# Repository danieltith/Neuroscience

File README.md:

# Neuroscience

Code and hardware files related to my PhD thesis: "Mapping associations between early life adversity and alcohol use disorder through human epidemiology and rat neurobiology".

[Link to be inserted once publicly available]

References:

Brown LA, Hasan S, Foster RG and Peirson SN. COMPASS: Continuous Open Mouse Phenotyping of Activity and Sleep Status [version 2; peer review: 4 approved]. Wellcome Open Res (2017) 1:2. (https://doi.org/10.12688/wellcomeopenres.9892.2)

Akam T, Lustig A, Rowland JM, Kapanaiah SKT, Esteve-Agraz J, Panniello M, Márquez C, Kohl MM, Kätzel D, Costa RM, Walton ME. Open-source, Python-based, hardware and software for controlling behavioural neuroscience experiments. eLife (2022) 11:e67846. (https://doi.org/10.7554/eLife.67846)

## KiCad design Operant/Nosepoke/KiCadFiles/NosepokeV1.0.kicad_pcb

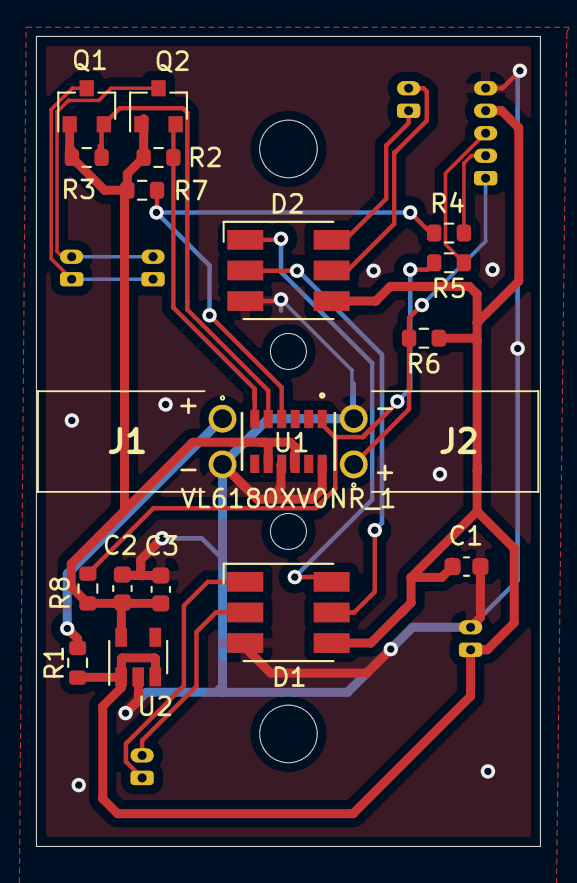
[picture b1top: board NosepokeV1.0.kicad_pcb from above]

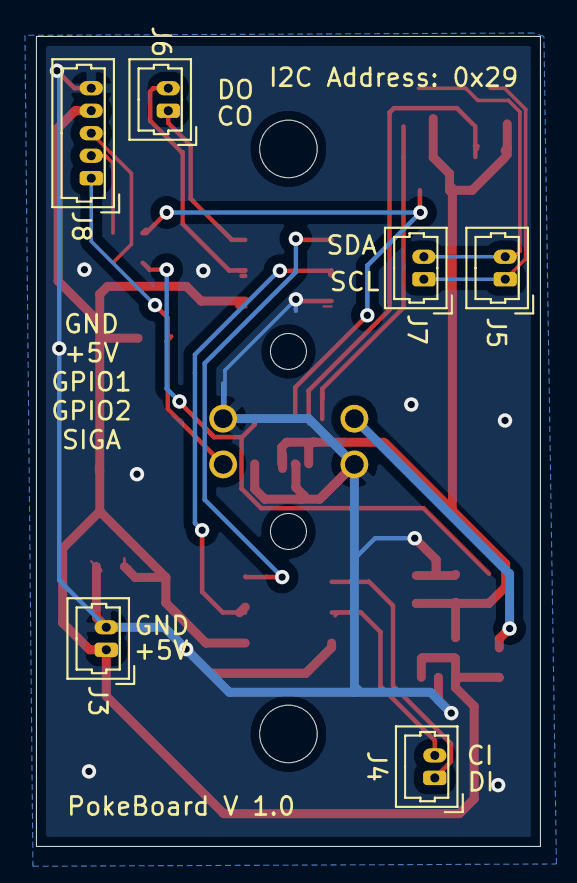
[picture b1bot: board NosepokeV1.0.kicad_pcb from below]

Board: 2 copper layers, 28.0 x 45.0 mm, 27 parts (6 on the bottom side), 19 nets.

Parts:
C1, C2: 10uF; C_0603_1608Metric
C3: 100nF; C_0603_1608Metric
D1: DotstarRGB; LED_RGB_5050-6
D2: DotstarWhite; LED_RGB_5050-6
J1, J2: SSW-102-02-T-S-RA; SSW-102-XX-YYY-S-RA
J3: 5V power in; Molex_PicoBlade_53047-0210_1x02_P1.25mm_Vertical
J4: SPI in; Molex_PicoBlade_53047-0210_1x02_P1.25mm_Vertical
J5: I2C in; Molex_PicoBlade_53047-0210_1x02_P1.25mm_Vertical
J6: SPI out; Molex_PicoBlade_53047-0210_1x02_P1.25mm_Vertical
J7: I2C out; Molex_PicoBlade_53047-0210_1x02_P1.25mm_Vertical
J8: Conn_01x03; Molex_PicoBlade_53047-0510_1x05_P1.25mm_Vertical
Mount1, Mount2: MountingHole_3.2mm_M3
Q1, Q2: BSS138; SOT-23
R1: 220R; R_0603_1608Metric
R2, R3, R4, R5, R6: 10K; R_0603_1608Metric
R7, R8: 47K; R_0603_1608Metric
U1: VL6180XV0NR_1; VL6180XV0NR&slash_1
U2: LP5907MFX-2.8; SOT-23-5

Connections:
+2V8: C2.1, C3.1, Q1.1, Q2.1, R2.1, R3.1, R7.1, R8.1, U1.8, U1.10, U2.5
+5V: C1.1, D1.4, D2.4, J3.1, J8.4, R1.1, R6.1, U2.1, U2.3
CI: D1.2, J4.2
CO: D2.5, J6.2
DI: D1.1, J4.1
DO: D2.6, J6.1
GND: C1.2, C2.2, C3.2, D1.3, D2.3, J1.2, J2.2, J3.2, J8.5, U1.9, U1.12, U2.2
GPIO0: J8.2, R4.1
GPIO1: J8.3, R5.1
unnamed: D1.5, D2.2
unnamed: D1.6, D2.1
unnamed: J1.1, R1.2
unnamed: R4.2, R7.2, U1.4
unnamed: R5.2, R8.2, U1.1
SCL: J5.1, J7.1, Q1.3
SCL_LV: Q1.2, R3.2, U1.5
SDA: J5.2, J7.2, Q2.3
SDA_LV: Q2.2, R2.2, U1.6
Sig_A: J2.1, J8.1, R6.2

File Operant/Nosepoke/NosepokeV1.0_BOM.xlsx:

Part Number | Designator | Description | Mount | Quantity | Manufacturer | Manufacturer PN | Supplier | Supplier PN
1 | C1,C2 | 10 uF Capacitor 0603 | SMD | 2 |  |  | Newbury free stock | 0603-10uF-6.3V
2 | C3 | 100nF Capacitor 0603 | SMD | 1 |  |  | Newbury free stock | 0603-100nF-25V
3 | J1,J2 | Right angle header | THT | 2 | SAMTEC | SSW-102-02-T-S-RA | Digikey | SAM11929-ND
4 | J3,J4,J5,J6,J7 | 2 pin connector | THT | 5 | Molex | 530470210 | Digikey | 455-1611-ND
5 | J8 | 5 pin connector | THT | 1 | Molex | 530470510 | Digikey | WM1734-ND
6 | Q1,Q2 | Mosfet | SMD | 2 |  | BSS138 | Farnell | 9845330
7 | R1 | 220R resistor 0603 | SMD | 1 |  |  | Newbury free stock | 0603-220R
8 | R2,R3,R4,R5,R6 | 10k resistor 0603 | SMD | 5 |  |  | Newbury free stock | 0603-10k
9 | R7,R8 | 47k resistor 0603 | SMD | 2 |  |  | Newbury free stock | 0603-47K
10 | U1 | TOF sensor | Leadless | 1 | ST Microelectronics | VL6180XV0NR/1 | Digikey | 497-14702-1-ND
11 | U2 | LP5907 2.8V LDO | SMD | 1 | TEXAS INSTRUMENTS | LP5907MFX-2.8/NOPB | Farnell | 3007717

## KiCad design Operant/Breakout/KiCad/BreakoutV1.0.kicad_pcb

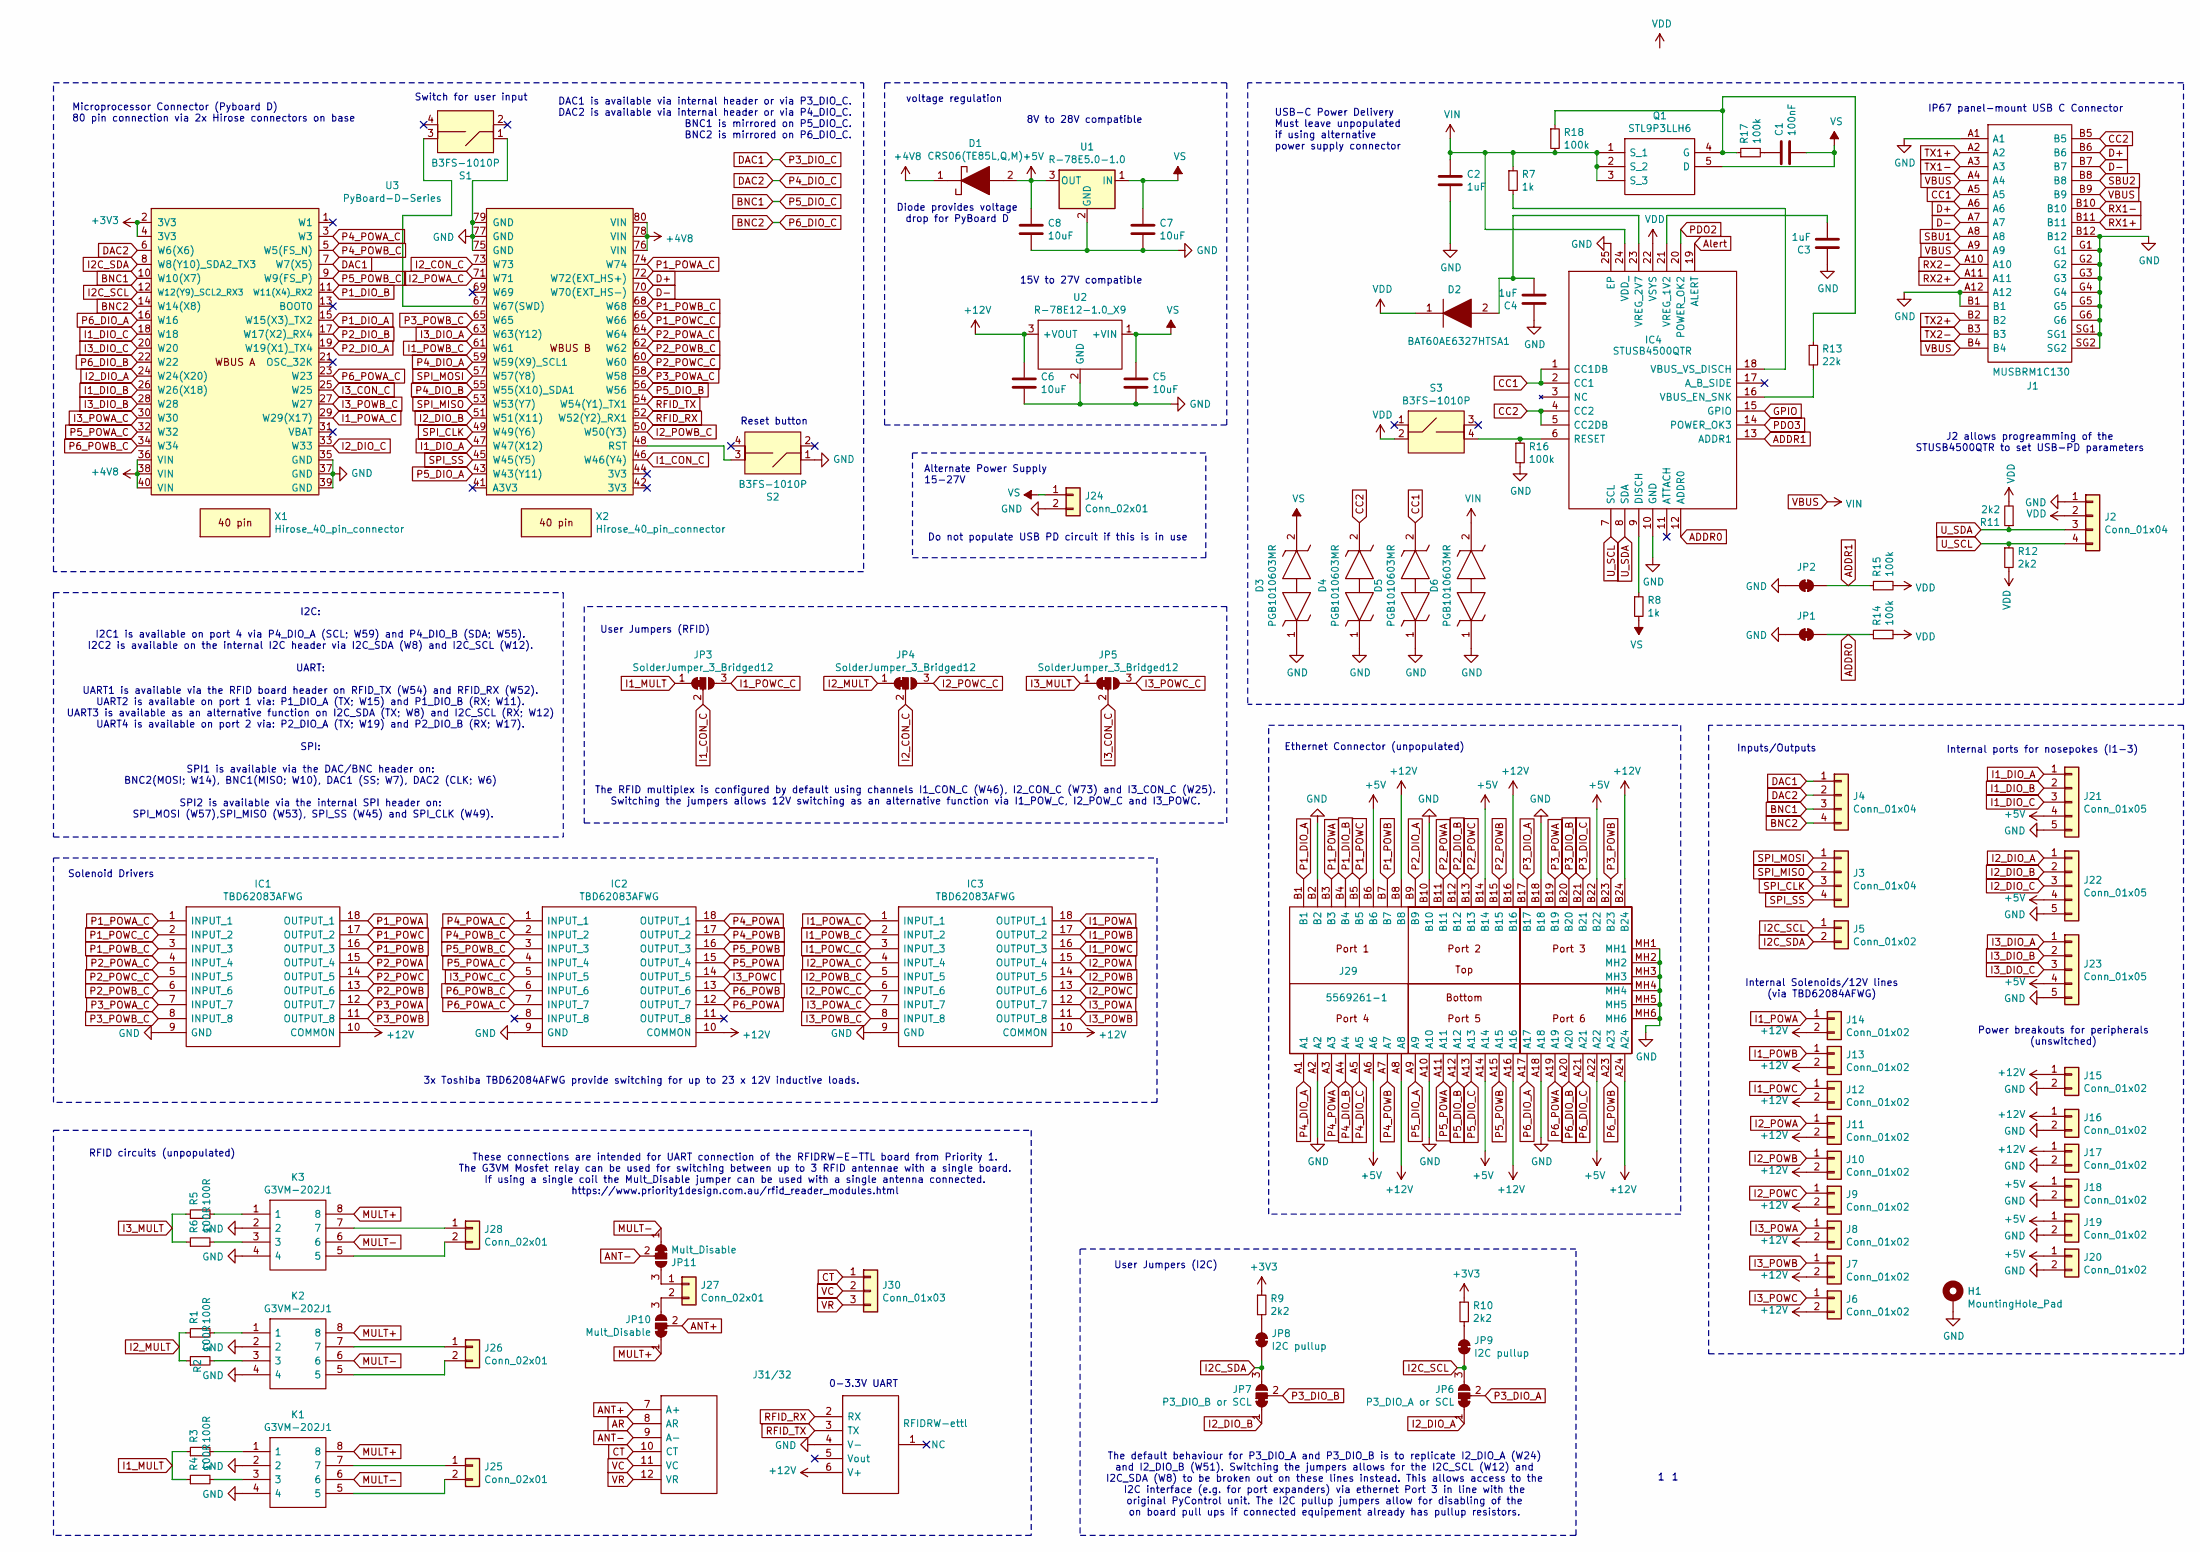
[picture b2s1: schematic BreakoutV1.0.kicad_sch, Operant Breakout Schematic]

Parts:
C1: 100nF; C_0805_2012Metric
C2, C3, C4: 1uF; C_0603_1608Metric
C5, C6, C7, C8: 10uF; C_1206_3216Metric
D1: CRS06(TE85L,Q,M); S-FLAT-2; Mouser Part Number 863-MBR120VLSFT3G
D2: BAT60AE6327HTSA1; SOD2513X110N; Mouser Part Number 726-BAT60AE6327HTSA1
D3, D4, D5, D6: PGB1010603MR; Mouser Part Number 576-PGB1010603MR
H1: MountingHole_Pad; SolderWirePad_single_1-2mmDrill
IC1, IC2, IC3: TBD62083AFWG; SOIC127P1030X245-18N; Mouser Part Number 757-TBD62083APG
IC4: STUSB4500QTR; QFN50P400X400X100-25N-D; Mouser Part Number 511-STUSB4500QTR
J1: MUSBRM1C130; Mouser Part Number 523-MUSBRM1C130
J2, J3, J4: Conn_01x04; Molex_PicoBlade_53047-0410_1x04_P1.25mm_Vertical
J5, J6, J7, J8, J9, J10, J11, J12, J13, J14, J15, J16, J17, J18, J19, J20: Conn_01x02; Molex_PicoBlade_53047-0210_1x02_P1.25mm_Vertical
J21, J22, J23: Conn_01x05; Molex_PicoBlade_53047-0510_1x05_P1.25mm_Vertical
J24, J25, J26, J27, J28: Conn_02x01; JST_EH_B2B-EH-A_1x02_P2.50mm_Vertical
J29: 5569261-1; 55692611; Mouser Part Number 571-5569261-1
J30: Conn_01x03; SolderWirePad_3x_0-8mmDrill2
J31/32: RFIDRW-ettl; Manufacturer_Part_Number RFIDRW-e-ttl
JP1, JP2: SolderJumper_2_Bridged; SolderJumper-2_P1.3mm_Bridged_RoundedPad1.0x1.5mm
JP3, JP4, JP5: SolderJumper_3_Bridged12; SolderJumper-3_P1.3mm_Bridged12_RoundedPad1.0x1.5mm_NumberL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
JP6: P3_DIO_A or SCL; SolderJumper-3_P1.3mm_Bridged12_RoundedPad1.0x1.5mm_NumberL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
JP7: P3_DIO_B or SCL; SolderJumper-3_P1.3mm_Bridged12_RoundedPad1.0x1.5mm_NumberL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
JP8, JP9: I2C pullup; SolderJumper-2_P1.3mm_Bridged_RoundedPad1.0x1.5mm
JP10, JP11: Mult_Disable; SolderJumper-3_P1.3mm_Bridged12_RoundedPad1.0x1.5mm_NumberL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
K1, K2, K3: G3VM-202J1; SOP254P700X210-8N; Mouser Part Number 653-G3VM-202J1
Q1: STL9P3LLH6; STL20N6F7; Mouser Part Number 511-STL9P3LLH6
R1, R2, R3, R4, R5, R6: 100R; R_0603_1608Metric
R7, R8: 1k; R_0603_1608Metric
R9, R10, R11, R12: 2k2; R_0603_1608Metric
R13: 22k; R_0603_1608Metric
R14, R15, R16, R17, R18: 100k; R_0603_1608Metric
S1, S2, S3: B3FS-1010P; 6mm_tactile_smd
U1: R-78E5.0-1.0; Converter_DCDC_RECOM_R-78E-0.5_THT
U2: R-78E12-1.0_X9; Converter_DCDC_RECOM_R-78E-0.5_THT; Mouser Part Number 919-R-78E12-1.0/X9
U3: PyBoard-D-Series; PyBoard_D-Series
X1, X2: Hirose_40_pin_connector; Hirose_40_pin

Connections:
+3V3: R9.1, R10.1, U3.2 (3V3), U3.4 (3V3)
+4V8: D1.1, U3.36 (VIN), U3.38 (VIN), U3.40 (VIN), U3.76 (VIN), U3.78 (VIN), U3.80 (VIN)
+5V: C8.1, D1.2, J18.1, J19.1, J20.1, J21.4, J22.4, J23.4, J29.A6, J29.A14, J29.A22, J29.B6, J29.B14, J29.B22, U1.3 (OUT)
+12V: C6.1, IC1.10 (COMMON), IC2.10 (COMMON), IC3.10 (COMMON), J6.2, J7.2, J8.2, J9.2, J10.2, J11.2, J12.2, J13.2, J14.2, J15.1, J16.1, J17.1, J29.A8, J29.A16, J29.A24, J29.B8, J29.B16, J29.B24, J31/32.6 (V+), U2.3 (+VOUT)
ADDR0: IC4.12 (ADDR0), JP1.1 (A), R14.1
ADDR1: IC4.13 (ADDR1), JP2.1 (A), R15.1
ANT+: J31/32.7 (A+), JP10.2 (C)
ANT-: J31/32.9 (A-), JP11.2 (C)
AR: J31/32.8 (AR)
Alert: IC4.19 (ALERT)
BNC1: J4.3, J29.A13, U3.10 (W10(X7))
BNC2: J4.4, J29.A21, U3.14 (W14(X8))
CC1: D5.2, IC4.1 (CC1DB), IC4.2 (CC1), J1.A5
CC2: D4.2, IC4.4 (CC2), IC4.5 (CC2DB), J1.B5
CT: J30.1, J31/32.10 (CT)
D+: J1.A6, J1.B6, U3.72 (W72(EXT_HS+))
D-: J1.A7, J1.B7, U3.70 (W70(EXT_HS-))
DAC1: J4.1, J29.B21, U3.7 (W7(X5))
DAC2: J4.2, J29.A5, U3.6 (W6(X6))
GND: C2.2, C3.1, C4.1, C5.2, C6.2, C7.2, C8.2, D3.1, D4.1, D5.1, D6.1, H1.1, IC1.9 (GND), IC2.9 (GND), IC3.9 (GND), IC4.10 (GND), IC4.25 (EP), J1.A1, J1.A12, J1.B1, J1.B12, J1.G1, J1.G2, J1.G3, J1.G4, J1.G5, J1.G6, J1.SG1, J1.SG2, J2.1, J15.2, J16.2, J17.2, J18.2, J19.2, J20.2, J21.5, J22.5, J23.5, J24.2, J29.A2, J29.A10, J29.A18, J29.B2, J29.B10, J29.B18, J29.MH1, J29.MH2, J29.MH3, J29.MH4, J29.MH5, J29.MH6, J31/32.4 (V-), JP1.2 (B), JP2.2 (B), K1.2, K1.4, K2.2, K2.4, K3.2, K3.4, R16.2, S1.1 (in1), S2.1 (in1), U1.2 (GND), U2.2 (GND), U3.35 (GND), U3.37 (GND), U3.39 (GND), U3.75 (GND), U3.77 (GND), U3.79 (GND)
GPIO: IC4.15 (GPIO)
I1_CON_C: JP3.2 (C), U3.46 (W46(Y4))
I1_DIO_A: J21.1, U3.47 (W47(X12))
I1_DIO_B: J21.2, U3.26 (W26(X18))
I1_DIO_C: J21.3, U3.18 (W18)
I1_MULT: JP3.1 (A), R3.1, R4.1
I1_POWA: IC3.18 (OUTPUT_1), J14.1
I1_POWA_C: IC3.1 (INPUT_1), U3.29 (W29(X17))
I1_POWB: IC3.17 (OUTPUT_2), J13.1
I1_POWB_C: IC3.2 (INPUT_2), U3.61 (W61)
I1_POWC: IC3.16 (OUTPUT_3), J12.1
I1_POWC_C: IC3.3 (INPUT_3), JP3.3 (B)
I2C_SCL: J5.1, JP6.3 (B), JP9.2 (B), U3.12 (W12(Y9)_SCL2_RX3)
I2C_SDA: J5.2, JP7.3 (B), JP8.2 (B), U3.8 (W8(Y10)_SDA2_TX3)
I2_CON_C: JP4.2 (C), U3.73 (W73)
I2_DIO_A: J22.1, JP6.1 (A), U3.24 (W24(X20))
I2_DIO_B: J22.2, JP7.1 (A), U3.51 (W51(X11))
I2_DIO_C: J22.3, U3.33 (W33)
I2_MULT: JP4.1 (A), R1.1, R2.1
I2_POWA: IC3.15 (OUTPUT_4), J11.1
I2_POWA_C: IC3.4 (INPUT_4), U3.71 (W71)
I2_POWB: IC3.14 (OUTPUT_5), J10.1
I2_POWB_C: IC3.5 (INPUT_5), U3.50 (W50(Y3))
I2_POWC: IC3.13 (OUTPUT_6), J9.1
I2_POWC_C: IC3.6 (INPUT_6), JP4.3 (B)
I3_CON_C: JP5.2 (C), U3.25 (W25)
I3_DIO_A: J23.1, U3.63 (W63(Y12))
I3_DIO_B: J23.2, U3.28 (W28)
I3_DIO_C: J23.3, U3.20 (W20)
I3_MULT: JP5.1 (A), R5.1, R6.1
I3_POWA: IC3.12 (OUTPUT_7), J8.1
I3_POWA_C: IC3.7 (INPUT_7), U3.30 (W30)
I3_POWB: IC3.11 (OUTPUT_8), J7.1
I3_POWB_C: IC3.8 (INPUT_8), U3.27 (W27)
I3_POWC: IC2.14 (OUTPUT_5), J6.1
I3_POWC_C: IC2.5 (INPUT_5), JP5.3 (B)
MULT+: JP10.1 (A), K1.8, K2.8, K3.8
MULT-: JP11.1 (A), K1.6, K2.6, K3.6
unnamed: C1.1, R17.2
unnamed: C3.2, IC4.21 (VREG_1V2)
unnamed: C4.2, D2.2, IC4.23 (VREG_2V7)
unnamed: IC4.6 (RESET), R16.1, S3.4 (out2)
unnamed: IC4.9 (DISCH), R8.1
unnamed: IC4.16 (VBUS_EN_SNK), R13.2
unnamed: IC4.18 (VBUS_VS_DISCH), R7.2
unnamed: J25.1, K1.7
unnamed: J25.2, K1.5
unnamed: J26.1, K2.7
unnamed: J26.2, K2.5
unnamed: J27.1, JP11.3 (B)
unnamed: J27.2, JP10.3 (B)
unnamed: J28.1, K3.7
unnamed: J28.2, K3.5
unnamed: JP8.1 (A), R9.2
unnamed: JP9.1 (A), R10.2
unnamed: K1.1, R3.2
unnamed: K1.3, R4.2
unnamed: K2.1, R1.2
unnamed: K2.3, R2.2
unnamed: K3.1, R5.2
unnamed: K3.3, R6.2
unnamed: Q1.4 (G), R13.1, R17.1, R18.1
unnamed: S1.3 (out1), U3.67 (W67(SWD))
unnamed: S2.3 (out1), U3.48 (RST)
P1_DIO_A: J29.B1, U3.15 (W15(X3)_TX2)
P1_DIO_B: J29.B4, U3.11 (W11(X4)_RX2)
P1_POWA: IC1.18 (OUTPUT_1), J29.B3
P1_POWA_C: IC1.1 (INPUT_1), U3.74 (W74)
P1_POWB: IC1.16 (OUTPUT_3), J29.B7
P1_POWB_C: IC1.3 (INPUT_3), U3.68 (W68)
P1_POWC: IC1.17 (OUTPUT_2), J29.B5
P1_POWC_C: IC1.2 (INPUT_2), U3.66 (W66)
P2_DIO_A: J29.B9, U3.19 (W19(X1)_TX4)
P2_DIO_B: J29.B12, U3.17 (W17(X2)_RX4)
P2_POWA: IC1.15 (OUTPUT_4), J29.B11
P2_POWA_C: IC1.4 (INPUT_4), U3.64 (W64)
P2_POWB: IC1.13 (OUTPUT_6), J29.B15
P2_POWB_C: IC1.6 (INPUT_6), U3.62 (W62)
P2_POWC: IC1.14 (OUTPUT_5), J29.B13
P2_POWC_C: IC1.5 (INPUT_5), U3.60 (W60)
P3_DIO_A: J29.B17, JP6.2 (C)
P3_DIO_B: J29.B20, JP7.2 (C)
P3_POWA: IC1.12 (OUTPUT_7), J29.B19
P3_POWA_C: IC1.7 (INPUT_7), U3.58 (W58)
P3_POWB: IC1.11 (OUTPUT_8), J29.B23
P3_POWB_C: IC1.8 (INPUT_8), U3.65 (W65)
P4_DIO_A: J29.A1, U3.59 (W59(X9)_SCL1)
P4_DIO_B: J29.A4, U3.55 (W55(X10)_SDA1)
P4_POWA: IC2.18 (OUTPUT_1), J29.A3
P4_POWA_C: IC2.1 (INPUT_1), U3.3 (W3)
P4_POWB: IC2.17 (OUTPUT_2), J29.A7
P4_POWB_C: IC2.2 (INPUT_2), U3.5 (W5(FS_N))
P5_DIO_A: J29.A9, U3.43 (W43(Y11))
P5_DIO_B: J29.A12, U3.56 (W56)
P5_POWA: IC2.15 (OUTPUT_4), J29.A11
P5_POWA_C: IC2.4 (INPUT_4), U3.32 (W32)
P5_POWB: IC2.16 (OUTPUT_3), J29.A15
P5_POWB_C: IC2.3 (INPUT_3), U3.9 (W9(FS_P))
P6_DIO_A: J29.A17, U3.16 (W16)
P6_DIO_B: J29.A20, U3.22 (W22)
P6_POWA: IC2.12 (OUTPUT_7), J29.A19
P6_POWA_C: IC2.7 (INPUT_7), U3.23 (W23)
P6_POWB: IC2.13 (OUTPUT_6), J29.A23
P6_POWB_C: IC2.6 (INPUT_6), U3.34 (W34)
PDO2: IC4.20 (POWER_OK2)
PDO3: IC4.14 (POWER_OK3)
RFID_RX: J31/32.2 (RX), U3.52 (W52(Y2)_RX1)
RFID_TX: J31/32.3 (TX), U3.54 (W54(Y1)_TX1)
RX1+: J1.B11
RX1-: J1.B10
RX2+: J1.A11
RX2-: J1.A10
SBU1: J1.A8
SBU2: J1.B8
SPI_CLK: J3.3, U3.49 (W49(Y6))
SPI_MISO: J3.2, U3.53 (W53(Y7))
SPI_MOSI: J3.1, U3.57 (W57(Y8))
SPI_SS: J3.4, U3.45 (W45(Y5))
TX1+: J1.A2
TX1-: J1.A3
TX2+: J1.B2
TX2-: J1.B3
U_SCL: IC4.7 (SCL), J2.4, R12.1
U_SDA: IC4.8 (SDA), J2.3, R11.1
VBUS: C2.1, D6.2, IC4.24 (VDD_), J1.A4, J1.A9, J1.B4, J1.B9, Q1.1 (S_1), Q1.2 (S_2), Q1.3 (S_3), R7.1, R18.2
VC: J30.2, J31/32.11 (VC)
VDD: D2.1, IC4.22 (VSYS), J2.2, R11.2, R12.2, R14.2, R15.2, S3.2 (in2)
VR: J30.3, J31/32.12 (VR)
VS: C1.2, C5.1, C7.1, D3.2, J24.1, Q1.5 (D), R8.2, U1.1 (IN), U2.1 (+VIN)

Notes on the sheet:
IP67 panel-mount USB C Connector
The RFID multiplex is configured by default using channels I1_CON_C (W46), I2_CON_C (W73) and I3_CON_C (W25). Switching the jumpers allows 12V switching as an alternative function via I1_POW_C, I2_POW_C and I3_POWC.
8V to 28V compatible
Alternate Power Supply 15-27V
J2 allows progreamming of the STUSB4500QTR to set USB-PD parameters
User Jumpers (RFID)
DAC1 is available via internal header or via P3_DIO_C. DAC2 is available via internal header or via P4_DIO_C. BNC1 is mirrored on P5_DIO_C. BNC2 is mirrored on P6_DIO_C.
3x Toshiba TBD62084AFWG provide switching for up to 23 x 12V inductive loads.
15V to 27V compatible
USB-C Power Delivery Must leave unpopulated if using alternative power supply connector
Do not populate USB PD circuit if this is in use
I2C: I2C1 is available on port 4 via P4_DIO_A (SCL; W59) and P4_DIO_B (SDA; W55). I2C2 is available on the internal I2C header via I2C_SDA (W8) and I2C_SCL (W12). UART: UART1 is available via the RFID board header on RFID_TX (W54) and RFID_RX (W52). UART2 is available on port 1 via: P1_DIO_A (TX; W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
User Jumpers (I2C)
Reset button
Switch for user input
Microprocessor Connector (Pyboard D) 80 pin connection via 2x Hirose connectors on base
voltage regulation
Diode provides voltage drop for PyBoard D
Ethernet Connector (unpopulated)
Power breakouts for peripherals (unswitched)
Internal ports for nosepokes (I1-3)
The default behaviour for P3_DIO_A and P3_DIO_B is to replicate I2_DIO_A (W24) and I2_DIO_B (W51). Switching the jumpers allows for the I2C_SCL (W12) and I2C_SDA (W8) to be broken out on these lines instead. This allows access to the I2C interface (e.g. for port expanders) via ethernet Port 3 in li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
Inputs/Outputs
Internal Solenoids/12V lines (via TBD62084AFWG)
RFID circuits (unpopulated)
These connections are intended for UART connection of the RFIDRW-E-TTL board from Priority 1. The G3VM Mosfet relay can be used for switching between up to 3 RFID antennae with a single board. If using a single coil the Mult_Disable jumper can be used with a single antenna connected. https://www.pr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
Solenoid Drivers
0-3.3V UART

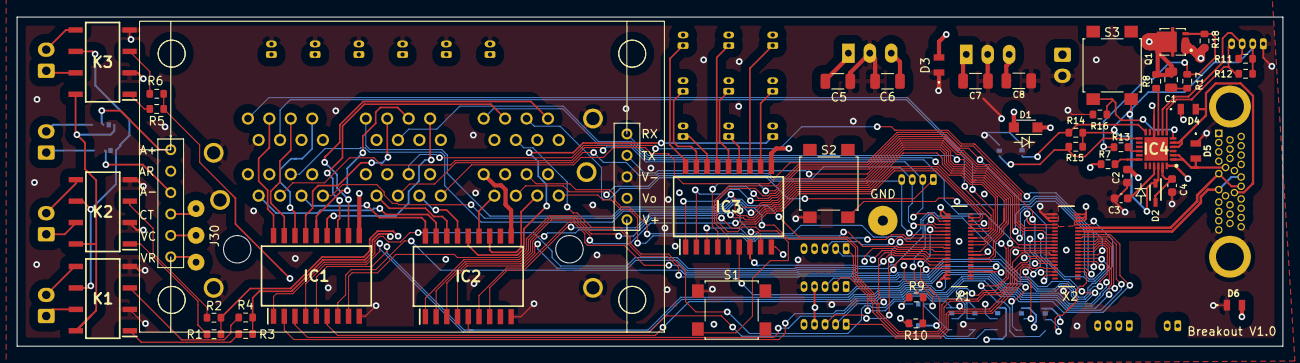
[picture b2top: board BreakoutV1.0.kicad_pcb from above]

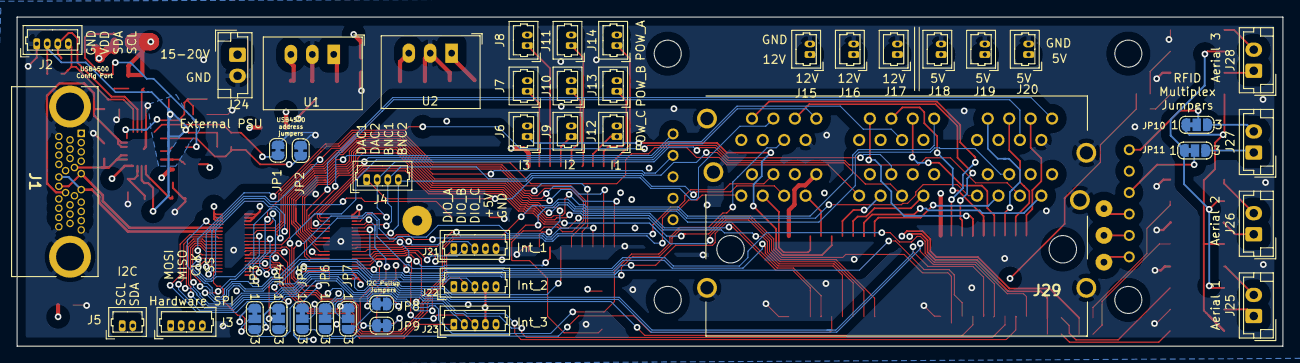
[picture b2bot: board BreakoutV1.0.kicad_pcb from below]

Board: 4 copper layers, 150.0 x 39.0 mm, 91 parts (42 on the bottom side), 134 nets.

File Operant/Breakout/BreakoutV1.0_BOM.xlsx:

Part Number | Designator | Description | Mount | Required Quantitiy | Manufacturer | Manufacturer PN | Supplier | Supplier PN
1 | C1 | Ceramic Capacitor 100V 100nF 0805 | SMD | 1 | KEMET | C0805C104K1RAC7210 | Digikey | 399-C0805C104K1RAC7210CT-ND
2 | C2,C3,C4 | Capacitor 16V 1uF 0603 | SMD | 3 |  |  | Newbury free stock | 0603-1uF-16V
3 | C5,C6,C7,C8 | Capacitor 25V 10uF 1206 | SMD | 4 |  |  | Newbury free stock | 1206-10uf-25V
4 | D1 | Diode Schottky 20V 1A | SMD | 1 | Toshiba | CRS06(TE85L,Q,M) | Digikey | CRS06QMCT-ND
5 | D2 | Diode Schottky 10V 3A | SMD | 1 | Infineon | BAT60AE6327HTSA1 | Digikey | BAT60AE6327HTSA1CT-ND
6 | D3,D4,D5,D6 | Diode TVS 24V 0603 | SMD | 4 | Littelfuse | PGB1010603MR | Digikey | F3801CT-ND
7 | IC1,IC2,IC3 | Driver Array | SMD | 3 | Toshiba | TBD62083AFWG | Digikey | TBD62083AFWGELCT-ND
8 | IC4 | USB TYPE-C PD CTRL, -40 TO 105DEG C | QFN | 1 | STMICROELECTRONICS | STUSB4500QTR | Digikey | 497-18060-1-ND
9 | J1 | USB-C connector | THT | 1 | Amphenol ICC (Commercial Products) | MUSBRM1C130 | Digikey | MUSBRM1C130-ND
10 | J2,J3,J4 | 4 pin through hole connector | THT | 3 | Molex | 530470410 | Digikey | WM1733-ND
11 | J5,J6,J7,J8,J9,J10,J11,J12,J13,J14,J15,J16,J17,J18,J19,J20 | 2 pin through hole connector | THT | 16 | Molex | 530470210 | Digikey | WM1731-ND
12 | J21,J22,J23 | 5 pin through hole connector | THT | 3 | Molex | 530470510 | Digikey | WM1734-ND
13 | Q1 | Power MOSFET | SMD | 1 | STMICROELECTRONICS | STL9P3LLH6 | Digikey | 497-17897-1-ND
14 | R1,R2,R3,R4,R5,R6 | 100 resistor; 0603; 0.1W | SMD | 6 |  |  | Newbury free stock | 0603-100R
15 | R7,R8 | 1k resistor; 0603; 0.1W | SMD | 2 |  |  | Newbury free stock | 0603-1K
16 | R9,R10,R11,R12 | 2.2k resistor; 0603; 0.1W | SMD | 4 |  |  | Newbury free stock | 0603-2K2
17 | R13 | 22k resistor; 0603; 0.1W | SMD | 1 |  |  | Newbury free stock | 0603-22K
18 | R14,R15,R16,R17,R18 | 100k resistor; 0603; 0.1W | SMD | 5 |  |  | Newbury free stock | 0603-100K
19 | S1,S2,S3 | SPST push switch | SMD | 3 | OMRON | B3FS-1012P | Digikey | SW1440CT-ND
20 | U1 | 5V 1A DC DC Converter | THT | 1 | Recom Power | R-78E5.0-1.0 | Digikey | 945-2201-ND
21 | U2 | 12V 1A DC DC Converter | THT | 1 | Recom Power | R-78E12-1.0/X9 | Digikey | 945-R-78E12-1.0/X9-ND
22 | X1,X2 | WBUS40 connector | SMD | 2 | Hirose Electric Co Ltd | DF40HC(4.0)-40DS-0.4V(70) | Digikey | H124604CT-ND

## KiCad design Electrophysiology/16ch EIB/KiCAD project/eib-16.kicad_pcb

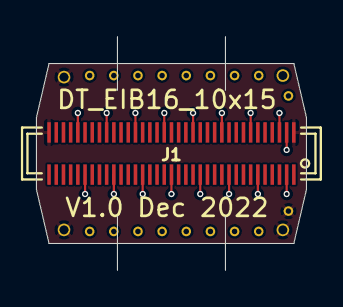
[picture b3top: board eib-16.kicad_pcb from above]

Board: 4 copper layers, 15.0 x 13.0 mm, 21 parts (0 on the bottom side), 17 nets.

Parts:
GND0: LRG_GP; GOLDPIN_0.5ID_0.7OD
GND1: LFP; GOLDPIN_0.5ID_0.7OD
J1: DF40-REC; DF40-70REC
LFP1, LFP2, LFP3, LFP4, LFP5, LFP6, LFP7, LFP8, LFP9, LFP10, LFP11, LFP12, LFP13, LFP14, LFP15: 1; LFP_Port
LFP16: 0; LFP_Port
REF1: LFP; GOLDPIN_0.5ID_0.7OD
SHLD_A1: LRG_GP; GOLDPIN_0.5ID_0.7OD

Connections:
GND: GND0.P$1 (0), GND1.P$1 (0), J1.36, J1.70, SHLD_A1.P$1 (0)
unnamed: J1.2, LFP1.0
unnamed: J1.6, LFP2.0
unnamed: J1.10, LFP3.0
unnamed: J1.14, LFP4.0
unnamed: J1.18, LFP5.0
unnamed: J1.22, LFP6.0
unnamed: J1.26, LFP7.0
unnamed: J1.30, LFP8.0
unnamed: J1.40, LFP16.0
unnamed: J1.44, LFP15.0
unnamed: J1.48, LFP14.0
unnamed: J1.52, LFP13.0
unnamed: J1.56, LFP12.0
unnamed: J1.60, LFP11.0
unnamed: J1.64, LFP10.0
unnamed: J1.68, LFP9.0

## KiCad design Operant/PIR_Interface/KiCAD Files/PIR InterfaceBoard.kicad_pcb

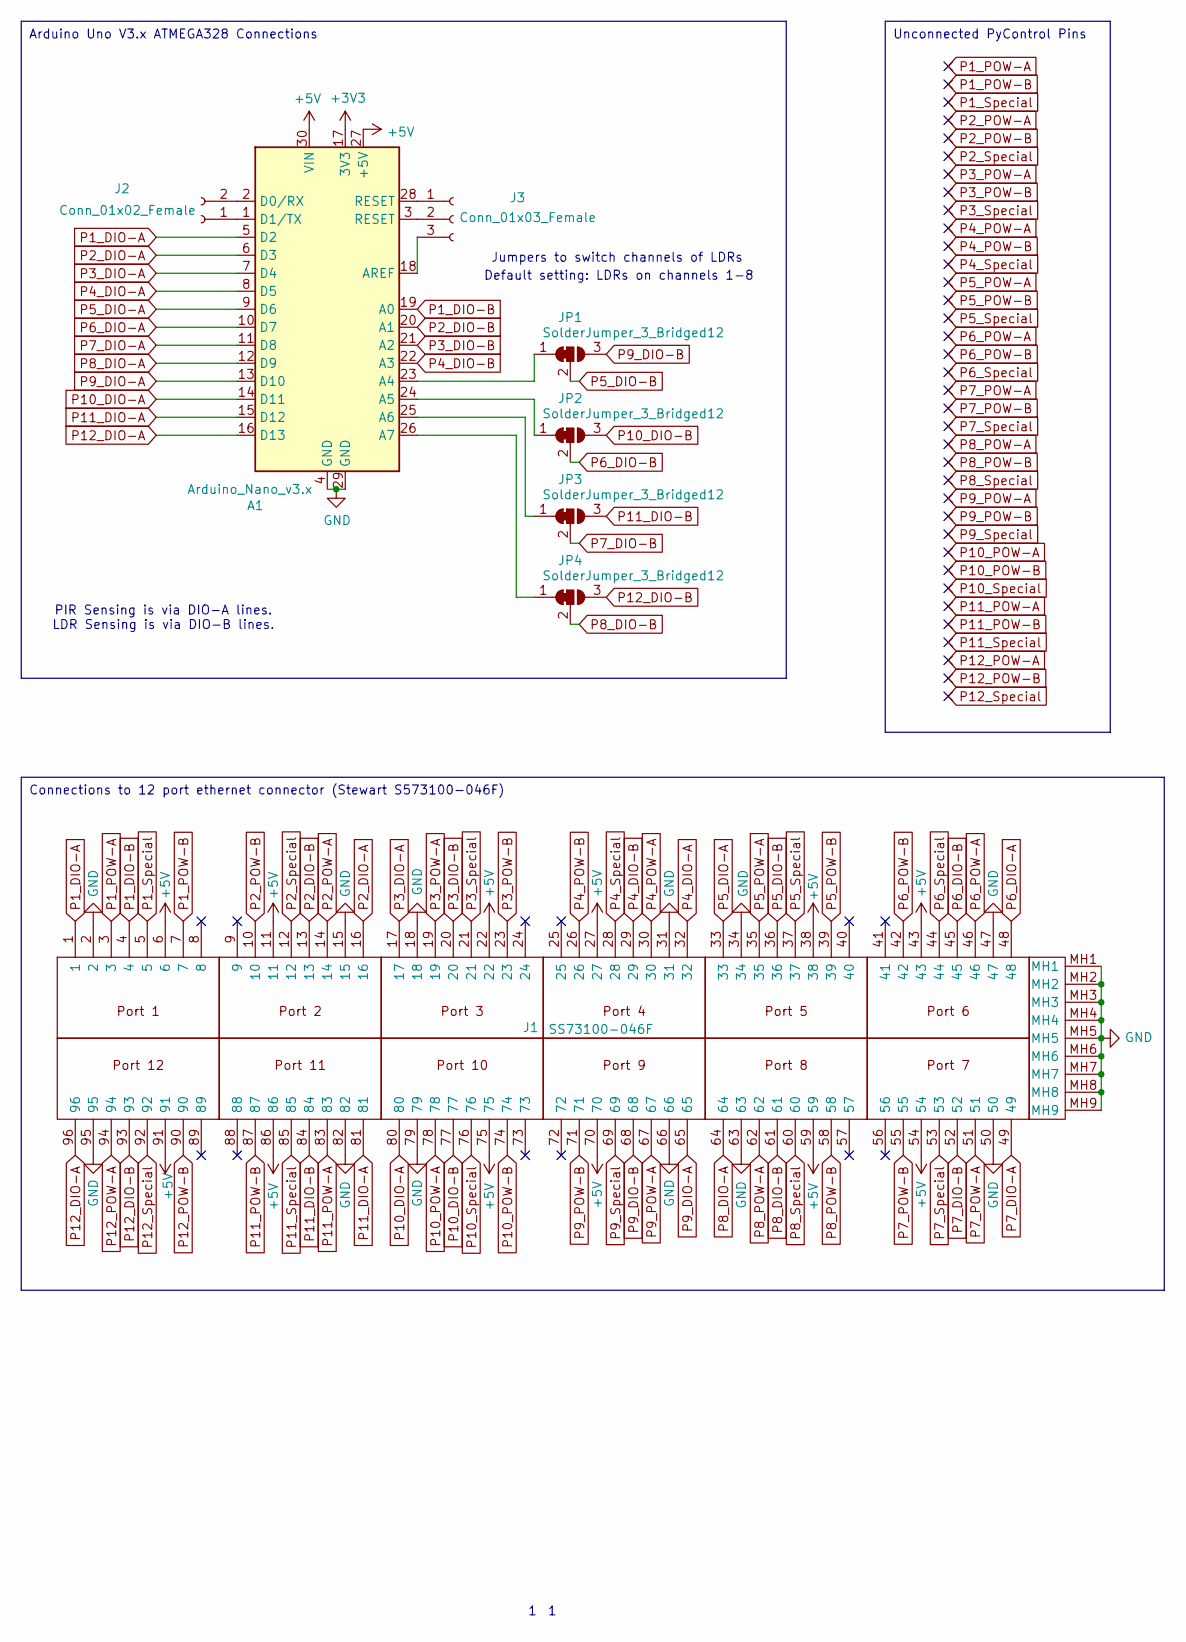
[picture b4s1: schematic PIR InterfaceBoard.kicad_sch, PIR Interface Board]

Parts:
A1: Arduino_Nano_v3.x; Arduino_Nano
J1: SS73100-046F; SS73100046F; Mouser Part Number 530-SS73100-046F
J2: Conn_01x02_Female; PinHeader_1x02_P2.54mm_Vertical
J3: Conn_01x03_Female; PinHeader_1x03_P2.54mm_Vertical
JP1, JP2, JP3, JP4: SolderJumper_3_Bridged12; SolderJumper-3_P1.3mm_Bridged12_RoundedPad1.0x1.5mm_NumberL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

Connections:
+3V3: A1.17 (3V3)
+5V: A1.27 (+5V), A1.30 (VIN), J1.6, J1.11, J1.22, J1.27, J1.38, J1.43, J1.54, J1.59, J1.70, J1.75, J1.86, J1.91
GND: A1.4 (GND), A1.29 (GND), J1.2, J1.15, J1.18, J1.31, J1.34, J1.47, J1.50, J1.63, J1.66, J1.79, J1.82, J1.95, J1.MH1, J1.MH2, J1.MH3, J1.MH4, J1.MH5, J1.MH6, J1.MH7, J1.MH8, J1.MH9
unnamed: A1.1 (D1/TX), J2.1
unnamed: A1.2 (D0/RX), J2.2
unnamed: A1.3 (RESET), J3.2
unnamed: A1.18 (AREF), J3.3
unnamed: A1.23 (A4), JP1.1 (A)
unnamed: A1.24 (A5), JP2.1 (A)
unnamed: A1.25 (A6), JP3.1 (A)
unnamed: A1.26 (A7), JP4.1 (A)
unnamed: A1.28 (RESET), J3.1
P1_DIO-A: A1.5 (D2), J1.1
P1_DIO-B: A1.19 (A0), J1.4
P1_POW-A: J1.3
P1_POW-B: J1.7
P1_Special: J1.5
P2_DIO-A: A1.6 (D3), J1.16
P2_DIO-B: A1.20 (A1), J1.13
P2_POW-A: J1.14
P2_POW-B: J1.10
P2_Special: J1.12
P3_DIO-A: A1.7 (D4), J1.17
P3_DIO-B: A1.21 (A2), J1.20
P3_POW-A: J1.19
P3_POW-B: J1.23
P3_Special: J1.21
P4_DIO-A: A1.8 (D5), J1.32
P4_DIO-B: A1.22 (A3), J1.29
P4_POW-A: J1.30
P4_POW-B: J1.26
P4_Special: J1.28
P5_DIO-A: A1.9 (D6), J1.33
P5_DIO-B: J1.36, JP1.2 (C)
P5_POW-A: J1.35
P5_POW-B: J1.39
P5_Special: J1.37
P6_DIO-A: A1.10 (D7), J1.48
P6_DIO-B: J1.45, JP2.2 (C)
P6_POW-A: J1.46
P6_POW-B: J1.42
P6_Special: J1.44
P7_DIO-A: A1.11 (D8), J1.49
P7_DIO-B: J1.52, JP3.2 (C)
P7_POW-A: J1.51
P7_POW-B: J1.55
P7_Special: J1.53
P8_DIO-A: A1.12 (D9), J1.64
P8_DIO-B: J1.61, JP4.2 (C)
P8_POW-A: J1.62
P8_POW-B: J1.58
P8_Special: J1.60
P9_DIO-A: A1.13 (D10), J1.65
P9_DIO-B: J1.68, JP1.3 (B)
P9_POW-A: J1.67
P9_POW-B: J1.71
P9_Special: J1.69
P10_DIO-A: A1.14 (D11), J1.80
P10_DIO-B: J1.77, JP2.3 (B)
P10_POW-A: J1.78
P10_POW-B: J1.74
P10_Special: J1.76
P11_DIO-A: A1.15 (D12), J1.81
P11_DIO-B: J1.84, JP3.3 (B)
P11_POW-A: J1.83
P11_POW-B: J1.87
P11_Special: J1.85
P12_DIO-A: A1.16 (D13), J1.96
P12_DIO-B: J1.93, JP4.3 (B)
P12_POW-A: J1.94
P12_POW-B: J1.90
P12_Special: J1.92

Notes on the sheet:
Arduino Uno V3.x ATMEGA328 Connections
Connections to 12 port ethernet connector (Stewart S573100-046F)
Unconnected PyControl Pins
Default setting: LDRs on channels 1-8
Jumpers to switch channels of LDRs
PIR Sensing is via DIO-A lines. LDR Sensing is via DIO-B lines.

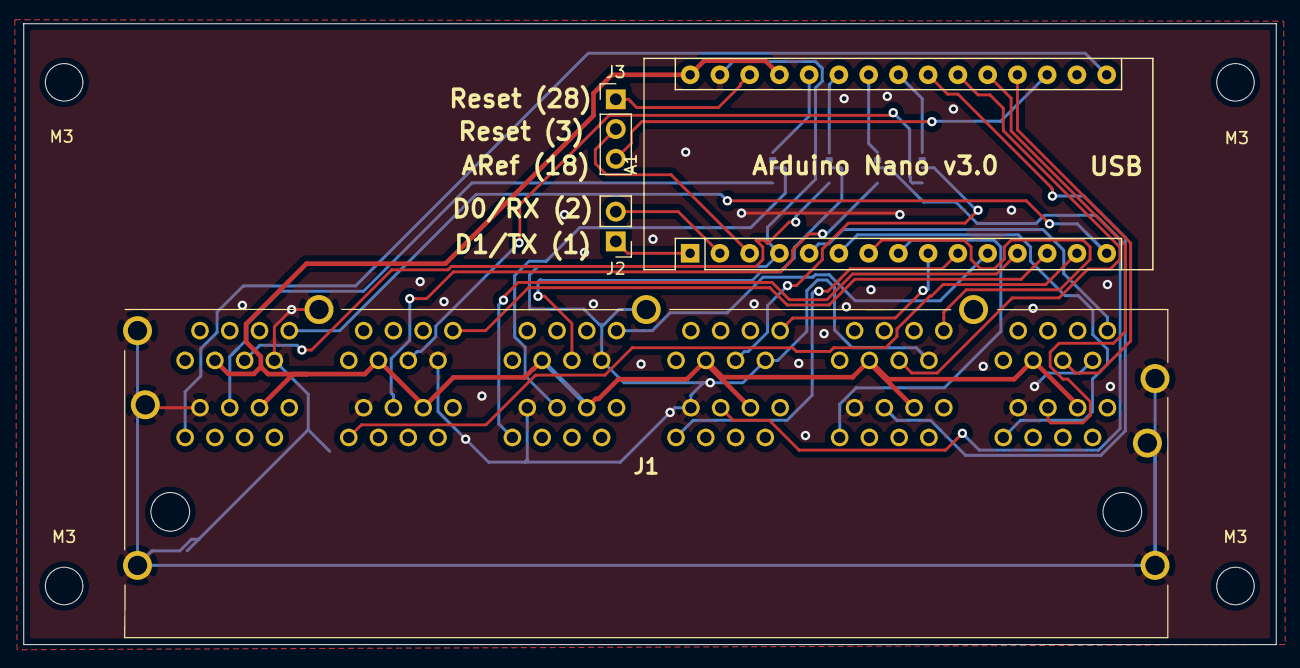
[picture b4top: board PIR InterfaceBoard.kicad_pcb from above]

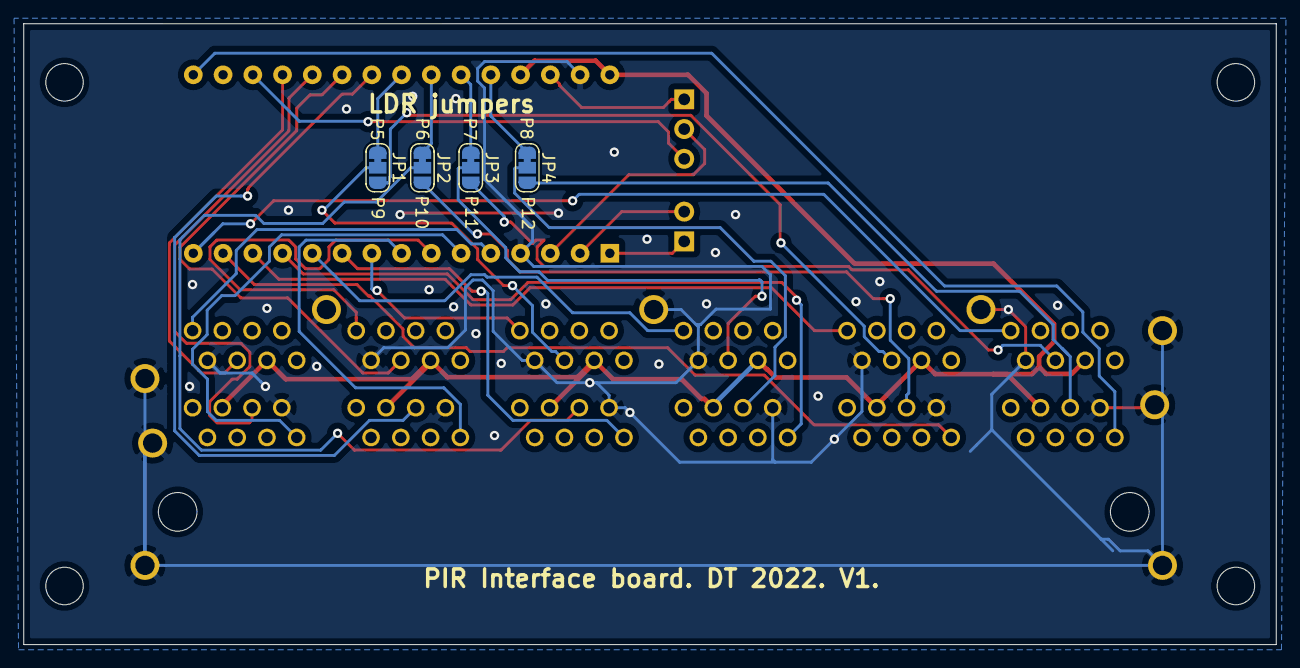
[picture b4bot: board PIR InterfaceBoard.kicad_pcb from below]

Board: 2 copper layers, 106.9 x 53.0 mm, 12 parts (4 on the bottom side), 35 nets.

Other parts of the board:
M3, M3#2, M3#3, M3#4: MountingHole_3.2mm_M3

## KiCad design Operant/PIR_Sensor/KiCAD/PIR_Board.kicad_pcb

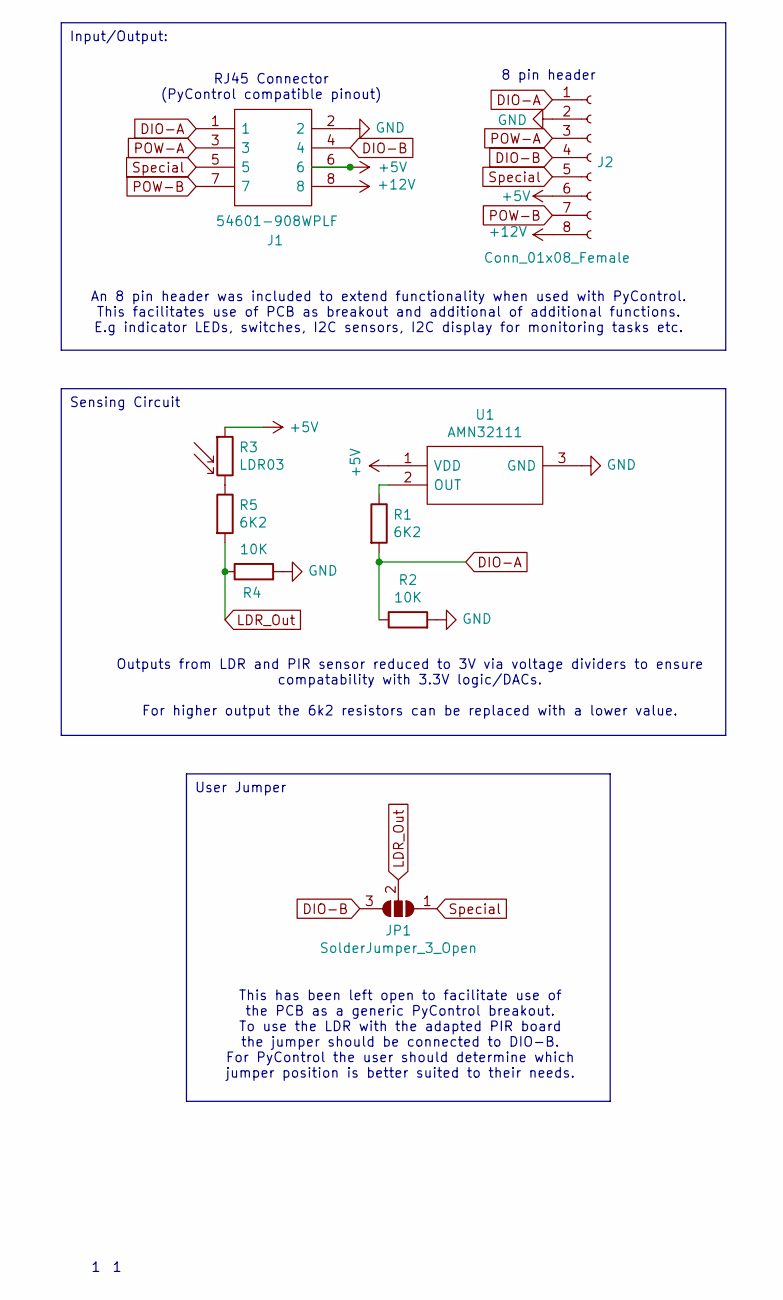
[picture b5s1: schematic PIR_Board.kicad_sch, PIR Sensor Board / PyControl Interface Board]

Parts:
J1: 54601-908WPLF; 54601908WPLF; Mouser Part Number 649-54601-908WPLF
J2: Conn_01x08_Female; PinSocket_1x08_P2.54mm_Vertical
JP1: SolderJumper_3_Open; SolderJumper-3_P1.3mm_Open_RoundedPad1.0x1.5mm_NumberLabels
R1, R5: 6K2; R_1206_3216Metric_Pad1.42x1.75mm_HandSolder
R2, R4: 10K; R_1206_3216Metric_Pad1.42x1.75mm_HandSolder
R3: LDR03; PinSocket_1x02_P2.54mm_Vertical
U1: AMN32111; AMN33111; Mouser Part Number 769-AMN32111

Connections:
+5V: J1.6, J2.6, R3.1, U1.1 (VDD)
+12V: J1.8, J2.8
DIO-A: J1.1, J2.1, R1.2, R2.1
DIO-B: J1.4, J2.4, JP1.3 (B)
GND: J1.2, J2.2, R2.2, R4.2, U1.3 (GND)
LDR_Out: JP1.2 (C), R4.1, R5.2
unnamed: R1.1, U1.2 (OUT)
unnamed: R3.2, R5.1
POW-A: J1.3, J2.3
POW-B: J1.7, J2.7
Special: J1.5, J2.5, JP1.1 (A)

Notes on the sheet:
Sensing Circuit
Input/Output:
User Jumper
An 8 pin header was included to extend functionality when used with PyControl. This facilitates use of PCB as breakout and additional of additional functions. E.g indicator LEDs, switches, I2C sensors, I2C display for monitoring tasks etc.
Outputs from LDR and PIR sensor reduced to 3V via voltage dividers to ensure compatability with 3.3V logic/DACs. For higher output the 6k2 resistors can be replaced with a lower value.
This has been left open to facilitate use of the PCB as a generic PyControl breakout. To use the LDR with the adapted PIR board the jumper should be connected to DIO-B. For PyControl the user should determine which jumper position is better suited to their needs.
RJ45 Connector (PyControl compatible pinout)
8 pin header

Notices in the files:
parts and their libraries:
Copyright 2016 Accelerated Designs. All rights reserved.
